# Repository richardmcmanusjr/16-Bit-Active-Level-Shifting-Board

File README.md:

# 16-Bit-Active-Level-Shifting-Board

This repository contains a 16-bit active level shifting board designed to interface a 16-bit adiabatic MIPS with a Virtex-7 VC707 FPGA. Active level shifting was required to convert the FPGA's 0 to +1.8V logic to the microprocessor's -0.6 to +0.6V logic. Comparators and a direction control unit was chosen for this purpose.

# Details

Schematic File:
  - 1-bit level shifting design block replicated 16 times
  - Power design block for regulated +/-1.5V and +3V
  - Direction controlling design block
  
Board File:
  - 2 layer board
  - 2 columns of 8 level shifting design blocks
  - 24-pin Molex ribbon cable connectors for input/output
  
# Design

### 1-Bit Active Level Shifter

# Layout 

### mainboard-01-8x2+1c.brd

### mainboard-01-8x2+1c OSHPARK

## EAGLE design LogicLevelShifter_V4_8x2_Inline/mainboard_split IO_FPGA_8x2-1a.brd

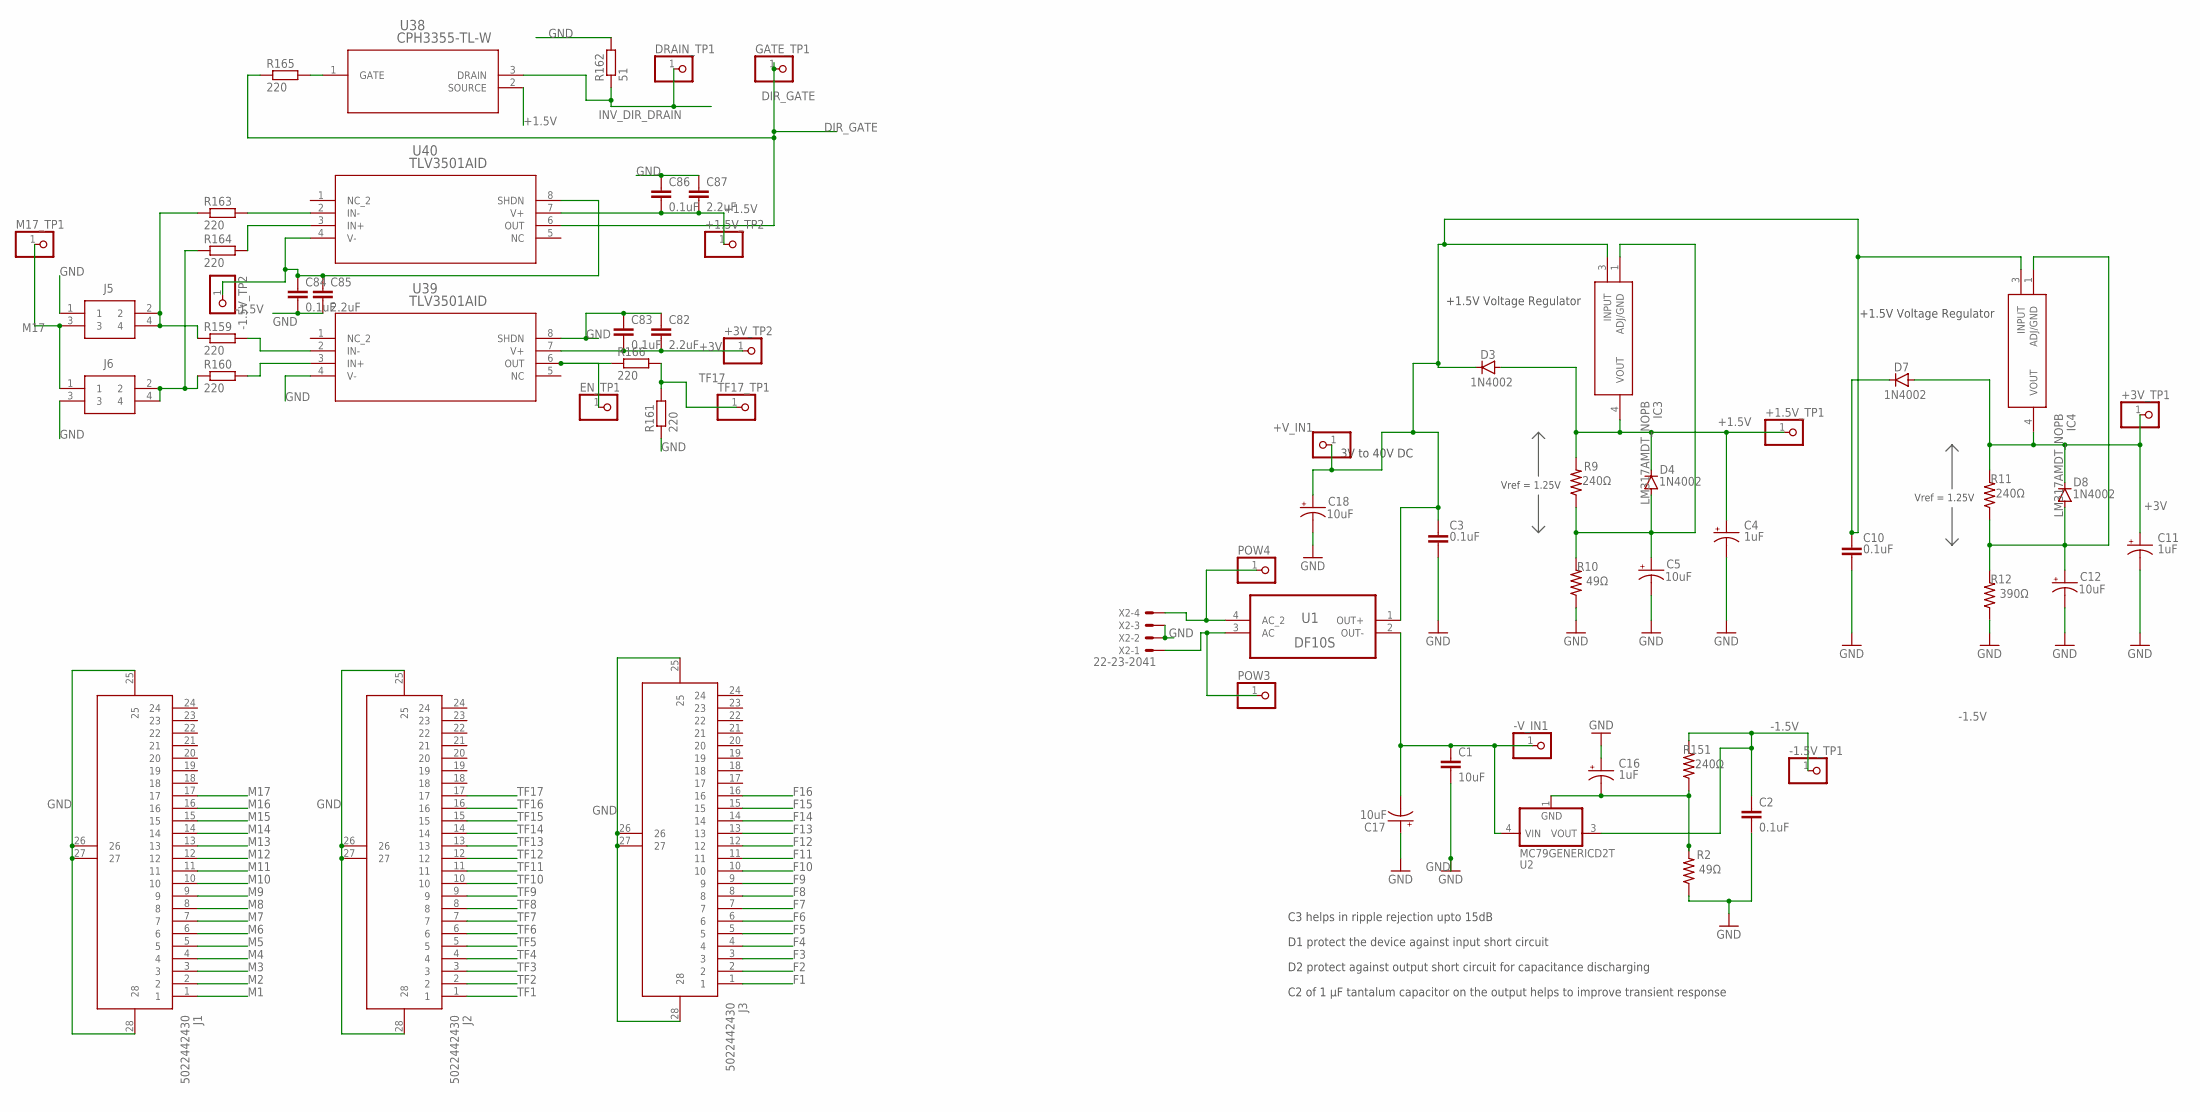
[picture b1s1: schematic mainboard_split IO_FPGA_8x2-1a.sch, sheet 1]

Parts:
+1.5V_TP1, +1.5V_TP2, +3V_TP1, +3V_TP2: PINHD-1X1; 1X01
+V_IN1: PINHD-1X1; 1X01
-1.5V_TP1, -1.5V_TP2: PINHD-1X1; 1X01
-V_IN1: PINHD-1X1; 1X01
C1: 10uF; C0805
C2, C83, C84, C86: 0.1uF; C0805
C3, C10: 0.1uF; C075-052X106
C4, C11, C16: 1uF; 085CS_1AR
C5, C12, C17, C18: 10uF; 085CS_1AR
C82, C85, C87: 2.2uF; C0805
D3, D4, D7, D8: 1N4002; DO41-10
DRAIN_TP1: PINHD-1X1; 1X01
EN_TP1: PINHD-1X1; 1X01
GATE_TP1: PINHD-1X1; 1X01
IC3, IC4: LM317AMDT_NOPB; TO228P991X238-3N
J1, J2, J3: 5022442430
J5, J6: 70287-1098; HDRV4W64P254_2X2_521X508X851P
M17_TP1: PINHD-1X1; 1X01
POW3, POW4: PINHD-1X1; 1X01
R2, R10: 49Ω; M0805
R9, R11, R151: 240Ω; M0805
R12: 390Ω; M0805
R159, R160, R161, R163, R164, R165, R166: 220; R0603
R162: 51; R0805
TF17_TP1: PINHD-1X1; 1X01
U1: DF10S; SOT508P985X260-4N
U2: MC79GENERICD2T; D2PAK-3
U38: CPH3355-TL-W; CPH3_2P9X1P6_ONS
U39, U40: TLV3501AID; D8
X2: 22-23-2041

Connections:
+1.5V: +1.5V_TP1.1, +1.5V_TP2.1, C4.+, C86.2, C87.2, D3.A, D4.C, IC3.4 (VOUT), R9.2, U38.2 (SOURCE), U40.7 (V+); also elsewhere on the board
+3V: +3V_TP1.1, +3V_TP2.1, C11.+, C82.2, C83.2, D7.A, D8.C, IC4.4 (VOUT), R11.2, U39.7 (V+); also elsewhere on the board
-1.5V: -1.5V_TP1.1, -1.5V_TP2.1, C2.1, C84.1, C85.1, R151.2, U2.3 (VOUT), U40.4 (V-), U40.8 (SHDN); also elsewhere on the board
DIR_GATE: GATE_TP1.1, R165.1, U40.6 (OUT); also elsewhere on the board
F1: J3.1; also elsewhere on the board
F2: J3.2; also elsewhere on the board
F3: J3.3; also elsewhere on the board
F4: J3.4; also elsewhere on the board
F5: J3.5; also elsewhere on the board
F6: J3.6; also elsewhere on the board
F7: J3.7; also elsewhere on the board
F8: J3.8; also elsewhere on the board
F9: J3.9; also elsewhere on the board
F10: J3.10; also elsewhere on the board
F11: J3.11; also elsewhere on the board
F12: J3.12; also elsewhere on the board
F13: J3.13; also elsewhere on the board
F14: J3.14; also elsewhere on the board
F15: J3.15; also elsewhere on the board
F16: J3.16; also elsewhere on the board
GND: C1.2, C2.2, C3.2, C4.-, C5.-, C10.2, C11.-, C12.-, C16.+, C17.+, C18.-, C82.1, C83.1, C84.2, C85.2, C86.1, C87.1, J1.25, J1.26, J1.27, J1.28, J2.25, J2.26, J2.27, J2.28, J3.25, J3.26, J3.27, J3.28, J5.1, J6.3, R2.1, R10.1, R12.1, R161.1, R162.2, U39.4 (V-), U39.8 (SHDN), X2.2, X2.3; also elsewhere on the board
INPPOS1: +V_IN1.1, C3.1, C10.1, C18.+, D3.C, D7.C, IC3.3 (INPUT), IC4.3 (INPUT), U1.1 (OUT+)
INV_DIR_DRAIN: DRAIN_TP1.1, R162.1, U38.3 (DRAIN); also elsewhere on the board
IN_2: POW3.1, U1.3 (AC), X2.1
M1: J1.1; also elsewhere on the board
M2: J1.2; also elsewhere on the board
M3: J1.3; also elsewhere on the board
M4: J1.4; also elsewhere on the board
M5: J1.5; also elsewhere on the board
M6: J1.6; also elsewhere on the board
M7: J1.7; also elsewhere on the board
M8: J1.8; also elsewhere on the board
M9: J1.9; also elsewhere on the board
M10: J1.10; also elsewhere on the board
M11: J1.11; also elsewhere on the board
M12: J1.12; also elsewhere on the board
M13: J1.13; also elsewhere on the board
M14: J1.14; also elsewhere on the board
M15: J1.15; also elsewhere on the board
M16: J1.16; also elsewhere on the board
M17: J1.17, J5.3, J6.1, M17_TP1.1
unnamed: C16.-, R2.2, R151.1, U2.1 (GND)
unnamed: C5.+, D4.A, IC3.1 (ADJ/GND), R9.1, R10.2
unnamed: C12.+, D8.A, IC4.1 (ADJ/GND), R11.1, R12.2
unnamed: POW4.1, U1.4 (AC_2), X2.4
unnamed: -V_IN1.1, C1.1, C17.-, U1.2 (OUT-), U2.4 (VIN)
unnamed: R159.2, U39.2 (IN-)
unnamed: R160.2, U39.3 (IN+)
unnamed: EN_TP1.1, R166.1, U39.6 (OUT)
unnamed: J6.2, J6.4, R160.1, R164.1
unnamed: J5.2, J5.4, R159.1, R163.1
unnamed: R163.2, U40.2 (IN-)
unnamed: R164.2, U40.3 (IN+)
unnamed: R165.2, U38.1 (GATE)
TF1: J2.1; also elsewhere on the board
TF2: J2.2; also elsewhere on the board
TF3: J2.3; also elsewhere on the board
TF4: J2.4; also elsewhere on the board
TF5: J2.5; also elsewhere on the board
TF6: J2.6; also elsewhere on the board
TF7: J2.7; also elsewhere on the board
TF8: J2.8; also elsewhere on the board
TF9: J2.9; also elsewhere on the board
TF10: J2.10; also elsewhere on the board
TF11: J2.11; also elsewhere on the board
TF12: J2.12; also elsewhere on the board
TF13: J2.13; also elsewhere on the board
TF14: J2.14; also elsewhere on the board
TF15: J2.15; also elsewhere on the board
TF16: J2.16; also elsewhere on the board
TF17: J2.17, R161.2, R166.2, TF17_TP1.1

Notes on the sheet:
+1.5V Voltage Regulator
3V to 40V DC
Vref = 1.25V
C3 helps in ripple rejection upto 15dB
D1 protect the device against input short circuit
D2 protect against output short circuit for capacitance discharging
C2 of 1 µF tantalum capacitor on the output helps to improve transient response

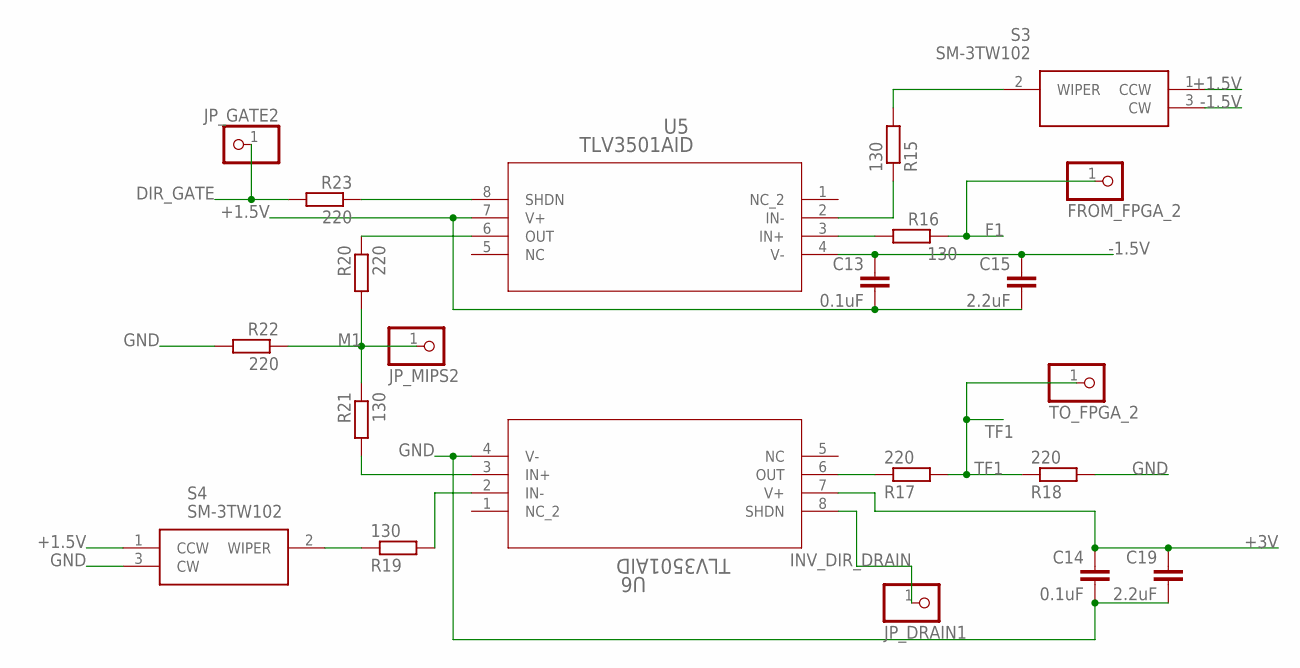
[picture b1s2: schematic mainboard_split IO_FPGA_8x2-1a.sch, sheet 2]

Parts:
C13, C14: 0.1uF; C0805
C15, C19: 2.2uF; C0805
FROM_FPGA_2: PINHD-1X1; 1X01
JP_DRAIN1: PINHD-1X1; 1X01
JP_GATE2: PINHD-1X1; 1X01
JP_MIPS2: PINHD-1X1; 1X01
R15, R19, R21: 130; R0805
R16: 130; R0603
R17, R18, R20, R22, R23: 220; R0805
S3, S4: SM-3TW102; SM3TW102
TO_FPGA_2: PINHD-1X1; 1X01
U5, U6: TLV3501AID; D8

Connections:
+1.5V: C13.2, C15.2, S3.1 (CCW), S4.1 (CCW), U5.7 (V+); also elsewhere on the board
+3V: C14.1, C19.1, U6.7 (V+); also elsewhere on the board
-1.5V: C13.1, C15.1, S3.3 (CW), U5.4 (V-); also elsewhere on the board
DIR_GATE: JP_GATE2.1, R23.2; also elsewhere on the board
F1: FROM_FPGA_2.1, R16.1; also elsewhere on the board
GND: C14.2, C19.2, R18.2, R22.2, S4.3 (CW), U6.4 (V-); also elsewhere on the board
INV_DIR_DRAIN: JP_DRAIN1.1, U6.8 (SHDN); also elsewhere on the board
M1: JP_MIPS2.1, R20.2, R21.1, R22.1; also elsewhere on the board
unnamed: R15.2, S3.2 (WIPER)
unnamed: R15.1, U5.2 (IN-)
unnamed: R17.1, U6.6 (OUT)
unnamed: R19.1, S4.2 (WIPER)
unnamed: R19.2, U6.2 (IN-)
unnamed: R21.2, U6.3 (IN+)
unnamed: R20.1, U5.6 (OUT)
unnamed: R23.1, U5.8 (SHDN)
unnamed: R16.2, U5.3 (IN+)
TF1: R17.2, R18.1, TO_FPGA_2.1; also elsewhere on the board

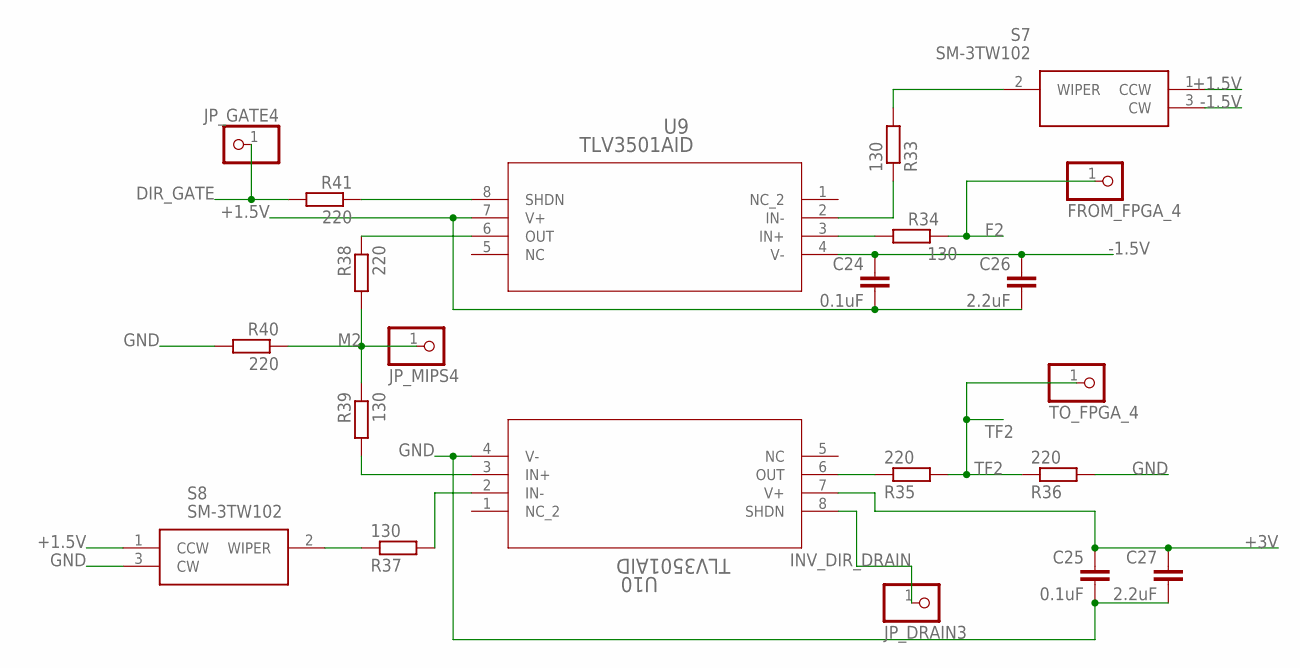
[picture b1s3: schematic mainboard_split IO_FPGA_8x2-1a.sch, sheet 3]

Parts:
C24, C25: 0.1uF; C0805
C26, C27: 2.2uF; C0805
FROM_FPGA_4: PINHD-1X1; 1X01
JP_DRAIN3: PINHD-1X1; 1X01
JP_GATE4: PINHD-1X1; 1X01
JP_MIPS4: PINHD-1X1; 1X01
R33, R37, R39: 130; R0805
R34: 130; R0603
R35, R36, R38, R40, R41: 220; R0805
S7, S8: SM-3TW102; SM3TW102
TO_FPGA_4: PINHD-1X1; 1X01
U9, U10: TLV3501AID; D8

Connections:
+1.5V: C24.2, C26.2, S7.1 (CCW), S8.1 (CCW), U9.7 (V+); also elsewhere on the board
+3V: C25.1, C27.1, U10.7 (V+); also elsewhere on the board
-1.5V: C24.1, C26.1, S7.3 (CW), U9.4 (V-); also elsewhere on the board
DIR_GATE: JP_GATE4.1, R41.2; also elsewhere on the board
F2: FROM_FPGA_4.1, R34.1; also elsewhere on the board
GND: C25.2, C27.2, R36.2, R40.2, S8.3 (CW), U10.4 (V-); also elsewhere on the board
INV_DIR_DRAIN: JP_DRAIN3.1, U10.8 (SHDN); also elsewhere on the board
M2: JP_MIPS4.1, R38.2, R39.1, R40.1; also elsewhere on the board
unnamed: R33.2, S7.2 (WIPER)
unnamed: R33.1, U9.2 (IN-)
unnamed: R35.1, U10.6 (OUT)
unnamed: R37.1, S8.2 (WIPER)
unnamed: R37.2, U10.2 (IN-)
unnamed: R39.2, U10.3 (IN+)
unnamed: R38.1, U9.6 (OUT)
unnamed: R41.1, U9.8 (SHDN)
unnamed: R34.2, U9.3 (IN+)
TF2: R35.2, R36.1, TO_FPGA_4.1; also elsewhere on the board

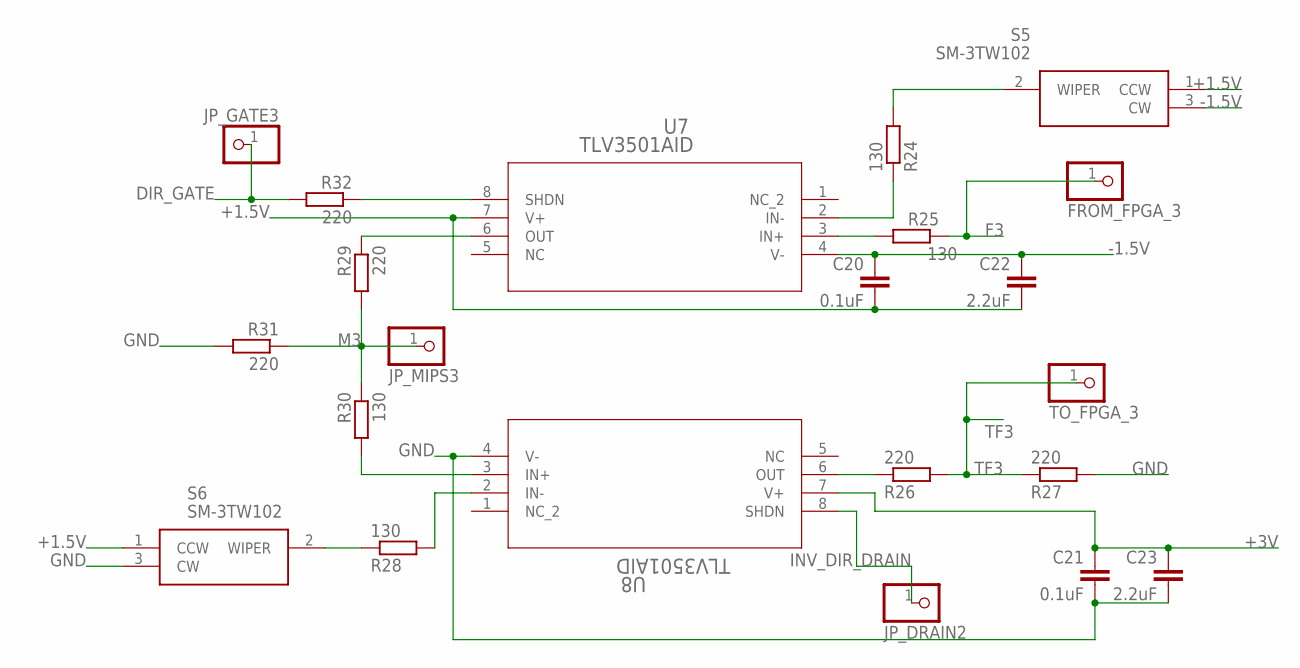
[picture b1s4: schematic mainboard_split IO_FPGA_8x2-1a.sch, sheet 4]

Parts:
C20, C21: 0.1uF; C0805
C22, C23: 2.2uF; C0805
FROM_FPGA_3: PINHD-1X1; 1X01
JP_DRAIN2: PINHD-1X1; 1X01
JP_GATE3: PINHD-1X1; 1X01
JP_MIPS3: PINHD-1X1; 1X01
R24, R28, R30: 130; R0805
R25: 130; R0603
R26, R27, R29, R31, R32: 220; R0805
S5, S6: SM-3TW102; SM3TW102
TO_FPGA_3: PINHD-1X1; 1X01
U7, U8: TLV3501AID; D8

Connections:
+1.5V: C20.2, C22.2, S5.1 (CCW), S6.1 (CCW), U7.7 (V+); also elsewhere on the board
+3V: C21.1, C23.1, U8.7 (V+); also elsewhere on the board
-1.5V: C20.1, C22.1, S5.3 (CW), U7.4 (V-); also elsewhere on the board
DIR_GATE: JP_GATE3.1, R32.2; also elsewhere on the board
F3: FROM_FPGA_3.1, R25.1; also elsewhere on the board
GND: C21.2, C23.2, R27.2, R31.2, S6.3 (CW), U8.4 (V-); also elsewhere on the board
INV_DIR_DRAIN: JP_DRAIN2.1, U8.8 (SHDN); also elsewhere on the board
M3: JP_MIPS3.1, R29.2, R30.1, R31.1; also elsewhere on the board
unnamed: R24.2, S5.2 (WIPER)
unnamed: R24.1, U7.2 (IN-)
unnamed: R26.1, U8.6 (OUT)
unnamed: R28.1, S6.2 (WIPER)
unnamed: R28.2, U8.2 (IN-)
unnamed: R30.2, U8.3 (IN+)
unnamed: R29.1, U7.6 (OUT)
unnamed: R32.1, U7.8 (SHDN)
unnamed: R25.2, U7.3 (IN+)
TF3: R26.2, R27.1, TO_FPGA_3.1; also elsewhere on the board

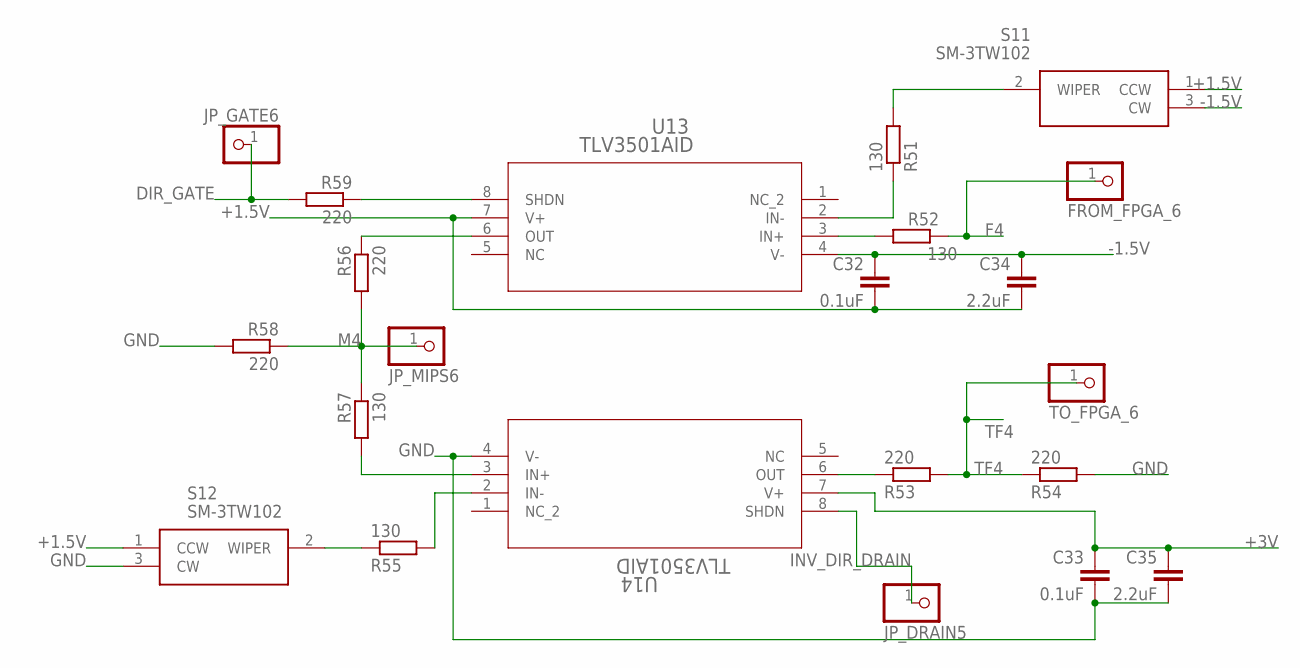
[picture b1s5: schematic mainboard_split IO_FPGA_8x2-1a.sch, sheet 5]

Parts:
C32, C33: 0.1uF; C0805
C34, C35: 2.2uF; C0805
FROM_FPGA_6: PINHD-1X1; 1X01
JP_DRAIN5: PINHD-1X1; 1X01
JP_GATE6: PINHD-1X1; 1X01
JP_MIPS6: PINHD-1X1; 1X01
R51, R55, R57: 130; R0805
R52: 130; R0603
R53, R54, R56, R58, R59: 220; R0805
S11, S12: SM-3TW102; SM3TW102
TO_FPGA_6: PINHD-1X1; 1X01
U13, U14: TLV3501AID; D8

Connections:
+1.5V: C32.2, C34.2, S11.1 (CCW), S12.1 (CCW), U13.7 (V+); also elsewhere on the board
+3V: C33.1, C35.1, U14.7 (V+); also elsewhere on the board
-1.5V: C32.1, C34.1, S11.3 (CW), U13.4 (V-); also elsewhere on the board
DIR_GATE: JP_GATE6.1, R59.2; also elsewhere on the board
F4: FROM_FPGA_6.1, R52.1; also elsewhere on the board
GND: C33.2, C35.2, R54.2, R58.2, S12.3 (CW), U14.4 (V-); also elsewhere on the board
INV_DIR_DRAIN: JP_DRAIN5.1, U14.8 (SHDN); also elsewhere on the board
M4: JP_MIPS6.1, R56.2, R57.1, R58.1; also elsewhere on the board
unnamed: R51.2, S11.2 (WIPER)
unnamed: R51.1, U13.2 (IN-)
unnamed: R53.1, U14.6 (OUT)
unnamed: R55.1, S12.2 (WIPER)
unnamed: R55.2, U14.2 (IN-)
unnamed: R57.2, U14.3 (IN+)
unnamed: R56.1, U13.6 (OUT)
unnamed: R59.1, U13.8 (SHDN)
unnamed: R52.2, U13.3 (IN+)
TF4: R53.2, R54.1, TO_FPGA_6.1; also elsewhere on the board

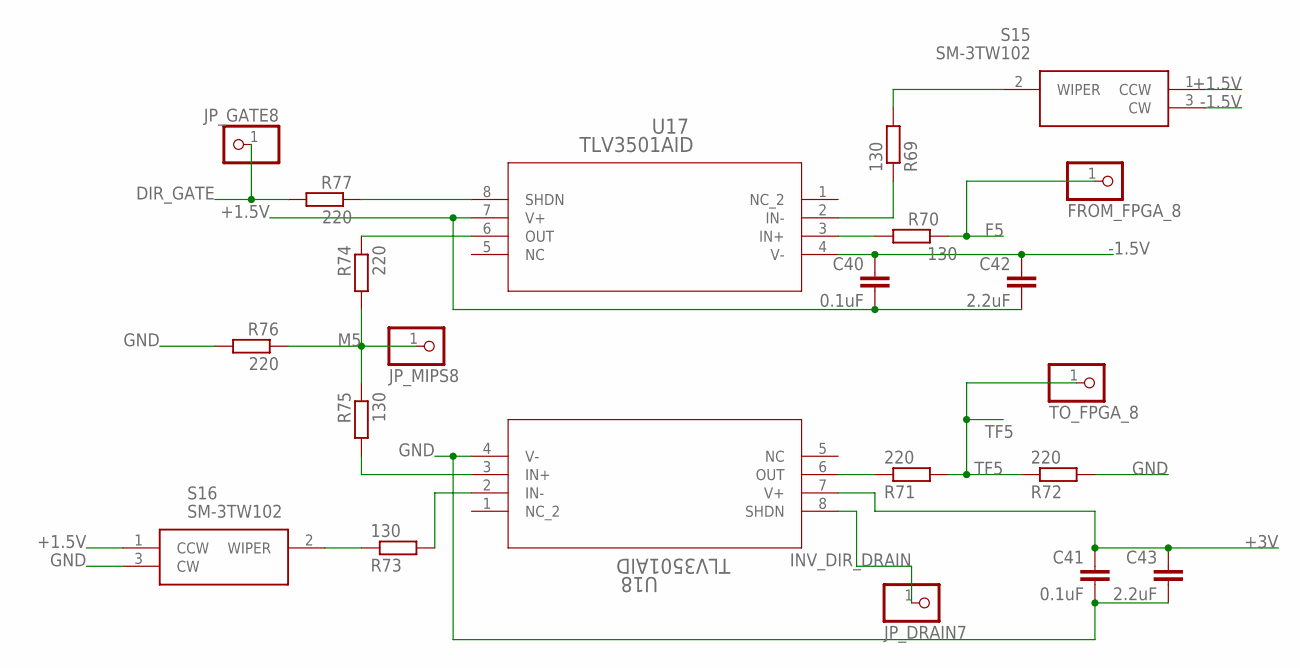
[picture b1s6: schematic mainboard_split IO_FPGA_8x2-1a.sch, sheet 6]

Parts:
C40, C41: 0.1uF; C0805
C42, C43: 2.2uF; C0805
FROM_FPGA_8: PINHD-1X1; 1X01
JP_DRAIN7: PINHD-1X1; 1X01
JP_GATE8: PINHD-1X1; 1X01
JP_MIPS8: PINHD-1X1; 1X01
R69, R73, R75: 130; R0805
R70: 130; R0603
R71, R72, R74, R76, R77: 220; R0805
S15, S16: SM-3TW102; SM3TW102
TO_FPGA_8: PINHD-1X1; 1X01
U17, U18: TLV3501AID; D8

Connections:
+1.5V: C40.2, C42.2, S15.1 (CCW), S16.1 (CCW), U17.7 (V+); also elsewhere on the board
+3V: C41.1, C43.1, U18.7 (V+); also elsewhere on the board
-1.5V: C40.1, C42.1, S15.3 (CW), U17.4 (V-); also elsewhere on the board
DIR_GATE: JP_GATE8.1, R77.2; also elsewhere on the board
F5: FROM_FPGA_8.1, R70.1; also elsewhere on the board
GND: C41.2, C43.2, R72.2, R76.2, S16.3 (CW), U18.4 (V-); also elsewhere on the board
INV_DIR_DRAIN: JP_DRAIN7.1, U18.8 (SHDN); also elsewhere on the board
M5: JP_MIPS8.1, R74.2, R75.1, R76.1; also elsewhere on the board
unnamed: R69.2, S15.2 (WIPER)
unnamed: R69.1, U17.2 (IN-)
unnamed: R71.1, U18.6 (OUT)
unnamed: R73.1, S16.2 (WIPER)
unnamed: R73.2, U18.2 (IN-)
unnamed: R75.2, U18.3 (IN+)
unnamed: R74.1, U17.6 (OUT)
unnamed: R77.1, U17.8 (SHDN)
unnamed: R70.2, U17.3 (IN+)
TF5: R71.2, R72.1, TO_FPGA_8.1; also elsewhere on the board

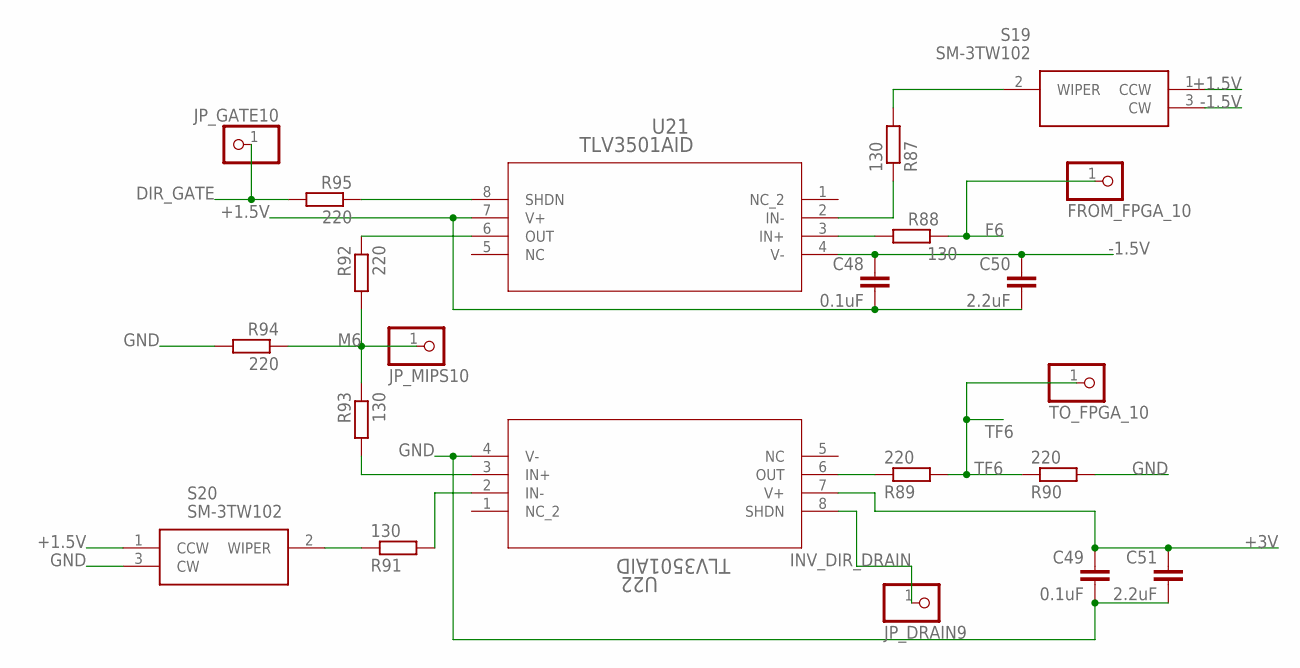
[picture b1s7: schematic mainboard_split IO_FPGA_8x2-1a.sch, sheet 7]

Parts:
C48, C49: 0.1uF; C0805
C50, C51: 2.2uF; C0805
FROM_FPGA_10: PINHD-1X1; 1X01
JP_DRAIN9: PINHD-1X1; 1X01
JP_GATE10: PINHD-1X1; 1X01
JP_MIPS10: PINHD-1X1; 1X01
R87, R91, R93: 130; R0805
R88: 130; R0603
R89, R90, R92, R94, R95: 220; R0805
S19, S20: SM-3TW102; SM3TW102
TO_FPGA_10: PINHD-1X1; 1X01
U21, U22: TLV3501AID; D8

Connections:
+1.5V: C48.2, C50.2, S19.1 (CCW), S20.1 (CCW), U21.7 (V+); also elsewhere on the board
+3V: C49.1, C51.1, U22.7 (V+); also elsewhere on the board
-1.5V: C48.1, C50.1, S19.3 (CW), U21.4 (V-); also elsewhere on the board
DIR_GATE: JP_GATE10.1, R95.2; also elsewhere on the board
F6: FROM_FPGA_10.1, R88.1; also elsewhere on the board
GND: C49.2, C51.2, R90.2, R94.2, S20.3 (CW), U22.4 (V-); also elsewhere on the board
INV_DIR_DRAIN: JP_DRAIN9.1, U22.8 (SHDN); also elsewhere on the board
M6: JP_MIPS10.1, R92.2, R93.1, R94.1; also elsewhere on the board
unnamed: R87.2, S19.2 (WIPER)
unnamed: R87.1, U21.2 (IN-)
unnamed: R89.1, U22.6 (OUT)
unnamed: R91.1, S20.2 (WIPER)
unnamed: R91.2, U22.2 (IN-)
unnamed: R93.2, U22.3 (IN+)
unnamed: R92.1, U21.6 (OUT)
unnamed: R95.1, U21.8 (SHDN)
unnamed: R88.2, U21.3 (IN+)
TF6: R89.2, R90.1, TO_FPGA_10.1; also elsewhere on the board

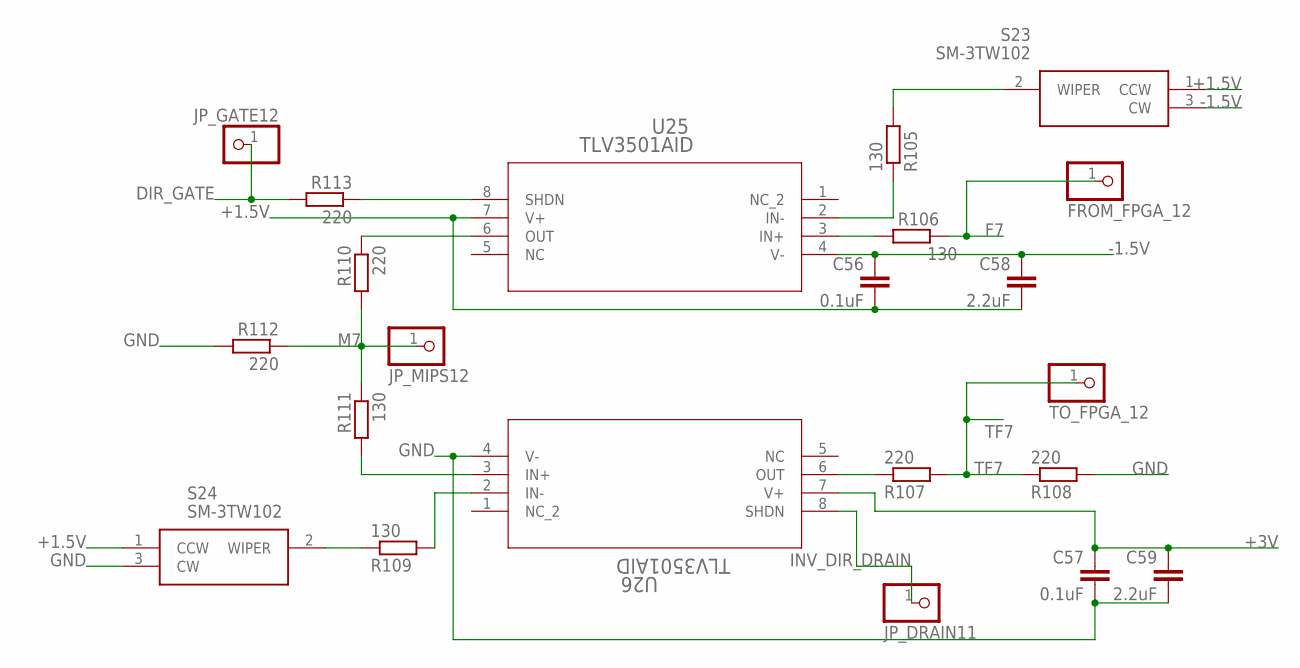
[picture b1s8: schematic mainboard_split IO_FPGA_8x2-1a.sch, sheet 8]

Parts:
C56, C57: 0.1uF; C0805
C58, C59: 2.2uF; C0805
FROM_FPGA_12: PINHD-1X1; 1X01
JP_DRAIN11: PINHD-1X1; 1X01
JP_GATE12: PINHD-1X1; 1X01
JP_MIPS12: PINHD-1X1; 1X01
R105, R109, R111: 130; R0805
R106: 130; R0603
R107, R108, R110, R112, R113: 220; R0805
S23, S24: SM-3TW102; SM3TW102
TO_FPGA_12: PINHD-1X1; 1X01
U25, U26: TLV3501AID; D8

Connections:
+1.5V: C56.2, C58.2, S23.1 (CCW), S24.1 (CCW), U25.7 (V+); also elsewhere on the board
+3V: C57.1, C59.1, U26.7 (V+); also elsewhere on the board
-1.5V: C56.1, C58.1, S23.3 (CW), U25.4 (V-); also elsewhere on the board
DIR_GATE: JP_GATE12.1, R113.2; also elsewhere on the board
F7: FROM_FPGA_12.1, R106.1; also elsewhere on the board
GND: C57.2, C59.2, R108.2, R112.2, S24.3 (CW), U26.4 (V-); also elsewhere on the board
INV_DIR_DRAIN: JP_DRAIN11.1, U26.8 (SHDN); also elsewhere on the board
M7: JP_MIPS12.1, R110.2, R111.1, R112.1; also elsewhere on the board
unnamed: R105.2, S23.2 (WIPER)
unnamed: R105.1, U25.2 (IN-)
unnamed: R107.1, U26.6 (OUT)
unnamed: R109.1, S24.2 (WIPER)
unnamed: R109.2, U26.2 (IN-)
unnamed: R111.2, U26.3 (IN+)
unnamed: R110.1, U25.6 (OUT)
unnamed: R113.1, U25.8 (SHDN)
unnamed: R106.2, U25.3 (IN+)
TF7: R107.2, R108.1, TO_FPGA_12.1; also elsewhere on the board

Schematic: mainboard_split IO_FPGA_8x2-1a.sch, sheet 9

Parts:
C64, C65: 0.1uF; C0805
C66, C67: 2.2uF; C0805
FROM_FPGA_14: PINHD-1X1; 1X01
JP_DRAIN13: PINHD-1X1; 1X01
JP_GATE14: PINHD-1X1; 1X01
JP_MIPS14: PINHD-1X1; 1X01
R123, R127, R129: 130; R0805
R124: 130; R0603
R125, R126, R128, R130, R131: 220; R0805
S27, S28: SM-3TW102; SM3TW102
TO_FPGA_14: PINHD-1X1; 1X01
U29, U30: TLV3501AID; D8

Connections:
+1.5V: C64.2, C66.2, S27.1 (CCW), S28.1 (CCW), U29.7 (V+); also elsewhere on the board
+3V: C65.1, C67.1, U30.7 (V+); also elsewhere on the board
-1.5V: C64.1, C66.1, S27.3 (CW), U29.4 (V-); also elsewhere on the board
DIR_GATE: JP_GATE14.1, R131.2; also elsewhere on the board
F8: FROM_FPGA_14.1, R124.1; also elsewhere on the board
GND: C65.2, C67.2, R126.2, R130.2, S28.3 (CW), U30.4 (V-); also elsewhere on the board
INV_DIR_DRAIN: JP_DRAIN13.1, U30.8 (SHDN); also elsewhere on the board
M8: JP_MIPS14.1, R128.2, R129.1, R130.1; also elsewhere on the board
unnamed: R123.2, S27.2 (WIPER)
unnamed: R123.1, U29.2 (IN-)
unnamed: R125.1, U30.6 (OUT)
unnamed: R127.1, S28.2 (WIPER)
unnamed: R127.2, U30.2 (IN-)
unnamed: R129.2, U30.3 (IN+)
unnamed: R128.1, U29.6 (OUT)
unnamed: R131.1, U29.8 (SHDN)
unnamed: R124.2, U29.3 (IN+)
TF8: R125.2, R126.1, TO_FPGA_14.1; also elsewhere on the board

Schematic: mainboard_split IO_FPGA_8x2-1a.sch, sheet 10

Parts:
C72, C73: 0.1uF; C0805
C74, C75: 2.2uF; C0805
FROM_FPGA_16: PINHD-1X1; 1X01
JP_DRAIN15: PINHD-1X1; 1X01
JP_GATE16: PINHD-1X1; 1X01
JP_MIPS16: PINHD-1X1; 1X01
R141, R145, R147: 130; R0805
R142: 130; R0603
R143, R144, R146, R148, R149: 220; R0805
S31, S32: SM-3TW102; SM3TW102
TO_FPGA_16: PINHD-1X1; 1X01
U33, U34: TLV3501AID; D8

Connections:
+1.5V: C72.2, C74.2, S31.1 (CCW), S32.1 (CCW), U33.7 (V+); also elsewhere on the board
+3V: C73.1, C75.1, U34.7 (V+); also elsewhere on the board
-1.5V: C72.1, C74.1, S31.3 (CW), U33.4 (V-); also elsewhere on the board
DIR_GATE: JP_GATE16.1, R149.2; also elsewhere on the board
F9: FROM_FPGA_16.1, R142.1; also elsewhere on the board
GND: C73.2, C75.2, R144.2, R148.2, S32.3 (CW), U34.4 (V-); also elsewhere on the board
INV_DIR_DRAIN: JP_DRAIN15.1, U34.8 (SHDN); also elsewhere on the board
M9: JP_MIPS16.1, R146.2, R147.1, R148.1; also elsewhere on the board
unnamed: R141.2, S31.2 (WIPER)
unnamed: R141.1, U33.2 (IN-)
unnamed: R143.1, U34.6 (OUT)
unnamed: R145.1, S32.2 (WIPER)
unnamed: R145.2, U34.2 (IN-)
unnamed: R147.2, U34.3 (IN+)
unnamed: R146.1, U33.6 (OUT)
unnamed: R149.1, U33.8 (SHDN)
unnamed: R142.2, U33.3 (IN+)
TF9: R143.2, R144.1, TO_FPGA_16.1; also elsewhere on the board

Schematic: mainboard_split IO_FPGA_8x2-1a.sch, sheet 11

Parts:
C80, C81: 0.1uF; C0805
C88, C89: 2.2uF; C0805
FROM_FPGA_18: PINHD-1X1; 1X01
JP_DRAIN17: PINHD-1X1; 1X01
JP_GATE18: PINHD-1X1; 1X01
JP_MIPS18: PINHD-1X1; 1X01
R168, R172, R174: 130; R0805
R169: 130; R0603
R170, R171, R173, R175, R176: 220; R0805
S35, S36: SM-3TW102; SM3TW102
TO_FPGA_18: PINHD-1X1; 1X01
U37, U41: TLV3501AID; D8

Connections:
+1.5V: C80.2, C88.2, S35.1 (CCW), S36.1 (CCW), U37.7 (V+); also elsewhere on the board
+3V: C81.1, C89.1, U41.7 (V+); also elsewhere on the board
-1.5V: C80.1, C88.1, S35.3 (CW), U37.4 (V-); also elsewhere on the board
DIR_GATE: JP_GATE18.1, R176.2; also elsewhere on the board
F10: FROM_FPGA_18.1, R169.1; also elsewhere on the board
GND: C81.2, C89.2, R171.2, R175.2, S36.3 (CW), U41.4 (V-); also elsewhere on the board
INV_DIR_DRAIN: JP_DRAIN17.1, U41.8 (SHDN); also elsewhere on the board
M10: JP_MIPS18.1, R173.2, R174.1, R175.1; also elsewhere on the board
unnamed: R168.2, S35.2 (WIPER)
unnamed: R168.1, U37.2 (IN-)
unnamed: R170.1, U41.6 (OUT)
unnamed: R172.1, S36.2 (WIPER)
unnamed: R172.2, U41.2 (IN-)
unnamed: R174.2, U41.3 (IN+)
unnamed: R173.1, U37.6 (OUT)
unnamed: R176.1, U37.8 (SHDN)
unnamed: R169.2, U37.3 (IN+)
TF10: R170.2, R171.1, TO_FPGA_18.1; also elsewhere on the board

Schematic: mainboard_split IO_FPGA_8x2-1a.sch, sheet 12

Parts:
C28, C29: 0.1uF; C0805
C30, C31: 2.2uF; C0805
FROM_FPGA_5: PINHD-1X1; 1X01
JP_DRAIN4: PINHD-1X1; 1X01
JP_GATE5: PINHD-1X1; 1X01
JP_MIPS5: PINHD-1X1; 1X01
R42, R46, R48: 130; R0805
R43: 130; R0603
R44, R45, R47, R49, R50: 220; R0805
S9, S10: SM-3TW102; SM3TW102
TO_FPGA_5: PINHD-1X1; 1X01
U11, U12: TLV3501AID; D8

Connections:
+1.5V: C28.2, C30.2, S9.1 (CCW), S10.1 (CCW), U11.7 (V+); also elsewhere on the board
+3V: C29.1, C31.1, U12.7 (V+); also elsewhere on the board
-1.5V: C28.1, C30.1, S9.3 (CW), U11.4 (V-); also elsewhere on the board
DIR_GATE: JP_GATE5.1, R50.2; also elsewhere on the board
F11: FROM_FPGA_5.1, R43.1; also elsewhere on the board
GND: C29.2, C31.2, R45.2, R49.2, S10.3 (CW), U12.4 (V-); also elsewhere on the board
INV_DIR_DRAIN: JP_DRAIN4.1, U12.8 (SHDN); also elsewhere on the board
M11: JP_MIPS5.1, R47.2, R48.1, R49.1; also elsewhere on the board
unnamed: R42.2, S9.2 (WIPER)
unnamed: R42.1, U11.2 (IN-)
unnamed: R44.1, U12.6 (OUT)
unnamed: R46.1, S10.2 (WIPER)
unnamed: R46.2, U12.2 (IN-)
unnamed: R48.2, U12.3 (IN+)
unnamed: R47.1, U11.6 (OUT)
unnamed: R50.1, U11.8 (SHDN)
unnamed: R43.2, U11.3 (IN+)
TF11: R44.2, R45.1, TO_FPGA_5.1; also elsewhere on the board

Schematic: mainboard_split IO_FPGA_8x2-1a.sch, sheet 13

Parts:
C44, C45: 0.1uF; C0805
C46, C47: 2.2uF; C0805
FROM_FPGA_9: PINHD-1X1; 1X01
JP_DRAIN8: PINHD-1X1; 1X01
JP_GATE9: PINHD-1X1; 1X01
JP_MIPS9: PINHD-1X1; 1X01
R78, R82, R84: 130; R0805
R79: 130; R0603
R80, R81, R83, R85, R86: 220; R0805
S17, S18: SM-3TW102; SM3TW102
TO_FPGA_9: PINHD-1X1; 1X01
U19, U20: TLV3501AID; D8

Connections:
+1.5V: C44.2, C46.2, S17.1 (CCW), S18.1 (CCW), U19.7 (V+); also elsewhere on the board
+3V: C45.1, C47.1, U20.7 (V+); also elsewhere on the board
-1.5V: C44.1, C46.1, S17.3 (CW), U19.4 (V-); also elsewhere on the board
DIR_GATE: JP_GATE9.1, R86.2; also elsewhere on the board
F12: FROM_FPGA_9.1, R79.1; also elsewhere on the board
GND: C45.2, C47.2, R81.2, R85.2, S18.3 (CW), U20.4 (V-); also elsewhere on the board
INV_DIR_DRAIN: JP_DRAIN8.1, U20.8 (SHDN); also elsewhere on the board
M12: JP_MIPS9.1, R83.2, R84.1, R85.1; also elsewhere on the board
unnamed: R78.2, S17.2 (WIPER)
unnamed: R78.1, U19.2 (IN-)
unnamed: R80.1, U20.6 (OUT)
unnamed: R82.1, S18.2 (WIPER)
unnamed: R82.2, U20.2 (IN-)
unnamed: R84.2, U20.3 (IN+)
unnamed: R83.1, U19.6 (OUT)
unnamed: R86.1, U19.8 (SHDN)
unnamed: R79.2, U19.3 (IN+)
TF12: R80.2, R81.1, TO_FPGA_9.1; also elsewhere on the board

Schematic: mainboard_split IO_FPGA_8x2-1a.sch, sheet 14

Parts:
C36, C37: 0.1uF; C0805
C38, C39: 2.2uF; C0805
FROM_FPGA_7: PINHD-1X1; 1X01
JP_DRAIN6: PINHD-1X1; 1X01
JP_GATE7: PINHD-1X1; 1X01
JP_MIPS7: PINHD-1X1; 1X01
R60, R64, R66: 130; R0805
R61: 130; R0603
R62, R63, R65, R67, R68: 220; R0805
S13, S14: SM-3TW102; SM3TW102
TO_FPGA_7: PINHD-1X1; 1X01
U15, U16: TLV3501AID; D8

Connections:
+1.5V: C36.2, C38.2, S13.1 (CCW), S14.1 (CCW), U15.7 (V+); also elsewhere on the board
+3V: C37.1, C39.1, U16.7 (V+); also elsewhere on the board
-1.5V: C36.1, C38.1, S13.3 (CW), U15.4 (V-); also elsewhere on the board
DIR_GATE: JP_GATE7.1, R68.2; also elsewhere on the board
F13: FROM_FPGA_7.1, R61.1; also elsewhere on the board
GND: C37.2, C39.2, R63.2, R67.2, S14.3 (CW), U16.4 (V-); also elsewhere on the board
INV_DIR_DRAIN: JP_DRAIN6.1, U16.8 (SHDN); also elsewhere on the board
M13: JP_MIPS7.1, R65.2, R66.1, R67.1; also elsewhere on the board
unnamed: R60.2, S13.2 (WIPER)
unnamed: R60.1, U15.2 (IN-)
unnamed: R62.1, U16.6 (OUT)
unnamed: R64.1, S14.2 (WIPER)
unnamed: R64.2, U16.2 (IN-)
unnamed: R66.2, U16.3 (IN+)
unnamed: R65.1, U15.6 (OUT)
unnamed: R68.1, U15.8 (SHDN)
unnamed: R61.2, U15.3 (IN+)
TF13: R62.2, R63.1, TO_FPGA_7.1; also elsewhere on the board

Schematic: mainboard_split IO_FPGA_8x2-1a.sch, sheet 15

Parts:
C60, C61: 0.1uF; C0805
C62, C63: 2.2uF; C0805
FROM_FPGA_13: PINHD-1X1; 1X01
JP_DRAIN12: PINHD-1X1; 1X01
JP_GATE13: PINHD-1X1; 1X01
JP_MIPS13: PINHD-1X1; 1X01
R114, R118, R120: 130; R0805
R115: 130; R0603
R116, R117, R119, R121, R122: 220; R0805
S25, S26: SM-3TW102; SM3TW102
TO_FPGA_13: PINHD-1X1; 1X01
U27, U28: TLV3501AID; D8

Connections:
+1.5V: C60.2, C62.2, S25.1 (CCW), S26.1 (CCW), U27.7 (V+); also elsewhere on the board
+3V: C61.1, C63.1, U28.7 (V+); also elsewhere on the board
-1.5V: C60.1, C62.1, S25.3 (CW), U27.4 (V-); also elsewhere on the board
DIR_GATE: JP_GATE13.1, R122.2; also elsewhere on the board
F14: FROM_FPGA_13.1, R115.1; also elsewhere on the board
GND: C61.2, C63.2, R117.2, R121.2, S26.3 (CW), U28.4 (V-); also elsewhere on the board
INV_DIR_DRAIN: JP_DRAIN12.1, U28.8 (SHDN); also elsewhere on the board
M14: JP_MIPS13.1, R119.2, R120.1, R121.1; also elsewhere on the board
unnamed: R114.2, S25.2 (WIPER)
unnamed: R114.1, U27.2 (IN-)
unnamed: R116.1, U28.6 (OUT)
unnamed: R118.1, S26.2 (WIPER)
unnamed: R118.2, U28.2 (IN-)
unnamed: R120.2, U28.3 (IN+)
unnamed: R119.1, U27.6 (OUT)
unnamed: R122.1, U27.8 (SHDN)
unnamed: R115.2, U27.3 (IN+)
TF14: R116.2, R117.1, TO_FPGA_13.1; also elsewhere on the board

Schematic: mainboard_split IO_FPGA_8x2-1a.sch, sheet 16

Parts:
C76, C77: 0.1uF; C0805
C78, C79: 2.2uF; C0805
FROM_FPGA_17: PINHD-1X1; 1X01
JP_DRAIN16: PINHD-1X1; 1X01
JP_GATE17: PINHD-1X1; 1X01
JP_MIPS17: PINHD-1X1; 1X01
R150, R155, R157: 130; R0805
R152: 130; R0603
R153, R154, R156, R158, R167: 220; R0805
S33, S34: SM-3TW102; SM3TW102
TO_FPGA_17: PINHD-1X1; 1X01
U35, U36: TLV3501AID; D8

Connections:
+1.5V: C76.2, C78.2, S33.1 (CCW), S34.1 (CCW), U35.7 (V+); also elsewhere on the board
+3V: C77.1, C79.1, U36.7 (V+); also elsewhere on the board
-1.5V: C76.1, C78.1, S33.3 (CW), U35.4 (V-); also elsewhere on the board
DIR_GATE: JP_GATE17.1, R167.2; also elsewhere on the board
F15: FROM_FPGA_17.1, R152.1; also elsewhere on the board
GND: C77.2, C79.2, R154.2, R158.2, S34.3 (CW), U36.4 (V-); also elsewhere on the board
INV_DIR_DRAIN: JP_DRAIN16.1, U36.8 (SHDN); also elsewhere on the board
M15: JP_MIPS17.1, R156.2, R157.1, R158.1; also elsewhere on the board
unnamed: R150.2, S33.2 (WIPER)
unnamed: R150.1, U35.2 (IN-)
unnamed: R153.1, U36.6 (OUT)
unnamed: R155.1, S34.2 (WIPER)
unnamed: R155.2, U36.2 (IN-)
unnamed: R157.2, U36.3 (IN+)
unnamed: R156.1, U35.6 (OUT)
unnamed: R167.1, U35.8 (SHDN)
unnamed: R152.2, U35.3 (IN+)
TF15: R153.2, R154.1, TO_FPGA_17.1; also elsewhere on the board

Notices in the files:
parts and their libraries:
COPYRIGHT: Copyright (C) 2022 Ultra Librarian. All rights reserved.
COPYRIGHT: Copyright (C) 2023 Ultra Librarian. All rights reserved.
